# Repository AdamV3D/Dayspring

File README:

The 45° mounts needs to be mirrored pairs for each LED light strip

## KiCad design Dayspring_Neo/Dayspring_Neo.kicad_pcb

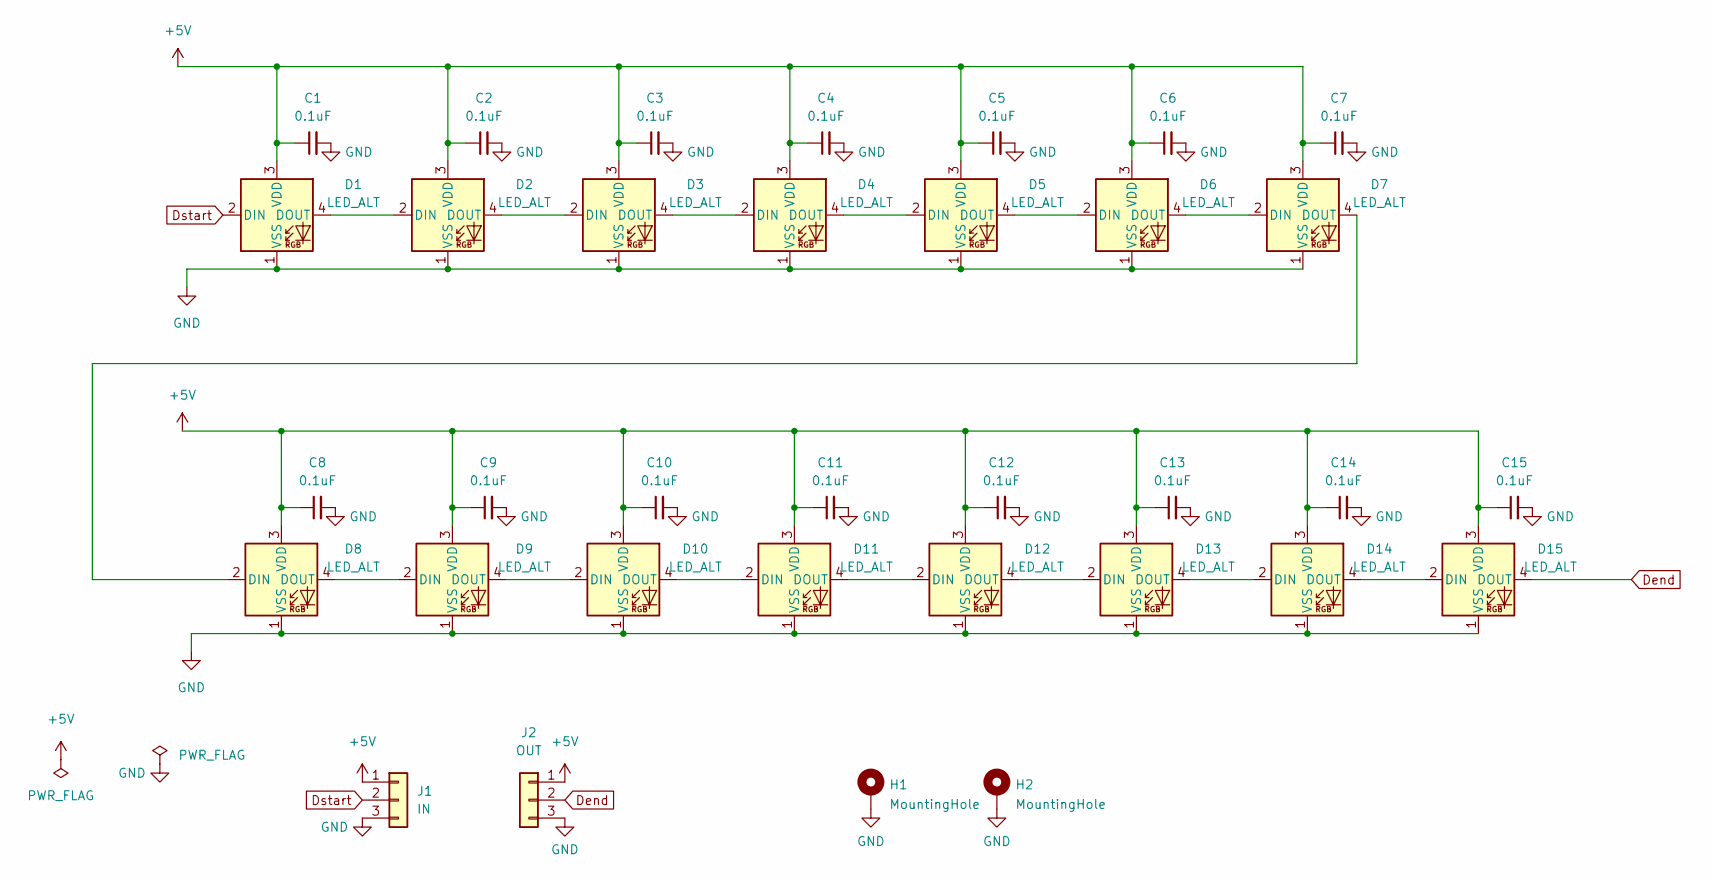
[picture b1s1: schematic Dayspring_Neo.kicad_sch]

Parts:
C1, C2, C3, C4, C5, C6, C7, C8, C9, C10, C11, C12, C13, C14, C15: 0.1uF; C_0805_2012Metric_Pad1.18x1.45mm_HandSolder_V3Dspec; LCSC C28233
D1, D2, D3, D4, D5, D6, D7, D8, D9, D10, D11, D12, D13, D14, D15: LED_ALT; XL-3528RGBW-WS2812B; LCSC C2890364
H1, H2: MountingHole; MountingHole_3.2mm_M3_Pad_Via
J1: IN; JST_XH_S3B-XH-A_1x03_P2.50mm_Horizontal
J2: OUT; JST_XH_S3B-XH-A_1x03_P2.50mm_Horizontal

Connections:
+5V: C1.1, C2.1, C3.1, C4.1, C5.1, C6.1, C7.1, C8.1, C9.1, C10.1, C11.1, C12.1, C13.1, C14.1, C15.1, D1.3 (VDD), D2.3 (VDD), D3.3 (VDD), D4.3 (VDD), D5.3 (VDD), D6.3 (VDD), D7.3 (VDD), D8.3 (VDD), D9.3 (VDD), D10.3 (VDD), D11.3 (VDD), D12.3 (VDD), D13.3 (VDD), D14.3 (VDD), D15.3 (VDD), J1.1, J2.1
Dend: D15.4 (DOUT), J2.2
Dstart: D1.2 (DIN), J1.2
GND: C1.2, C2.2, C3.2, C4.2, C5.2, C6.2, C7.2, C8.2, C9.2, C10.2, C11.2, C12.2, C13.2, C14.2, C15.2, D1.1 (VSS), D2.1 (VSS), D3.1 (VSS), D4.1 (VSS), D5.1 (VSS), D6.1 (VSS), D7.1 (VSS), D8.1 (VSS), D9.1 (VSS), D10.1 (VSS), D11.1 (VSS), D12.1 (VSS), D13.1 (VSS), D14.1 (VSS), D15.1 (VSS), H1.1, H2.1, J1.3, J2.3
unnamed: D1.4 (DOUT), D2.2 (DIN)
unnamed: D2.4 (DOUT), D3.2 (DIN)
unnamed: D3.4 (DOUT), D4.2 (DIN)
unnamed: D4.4 (DOUT), D5.2 (DIN)
unnamed: D5.4 (DOUT), D6.2 (DIN)
unnamed: D6.4 (DOUT), D7.2 (DIN)
unnamed: D7.4 (DOUT), D8.2 (DIN)
unnamed: D8.4 (DOUT), D9.2 (DIN)
unnamed: D9.4 (DOUT), D10.2 (DIN)
unnamed: D10.4 (DOUT), D11.2 (DIN)
unnamed: D11.4 (DOUT), D12.2 (DIN)
unnamed: D12.4 (DOUT), D13.2 (DIN)
unnamed: D13.4 (DOUT), D14.2 (DIN)
unnamed: D14.4 (DOUT), D15.2 (DIN)

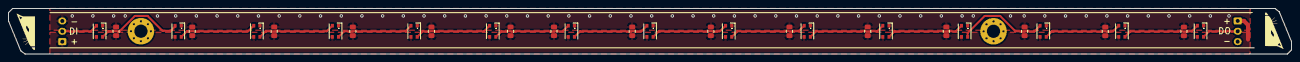
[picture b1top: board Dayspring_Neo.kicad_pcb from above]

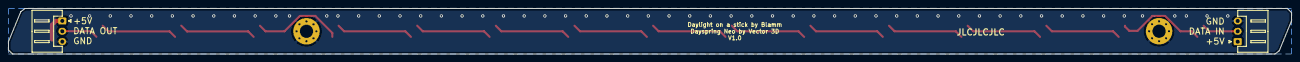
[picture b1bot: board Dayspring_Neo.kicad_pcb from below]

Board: 2 copper layers, 310.0 x 11.0 mm, 34 parts (2 on the bottom side), 18 nets.

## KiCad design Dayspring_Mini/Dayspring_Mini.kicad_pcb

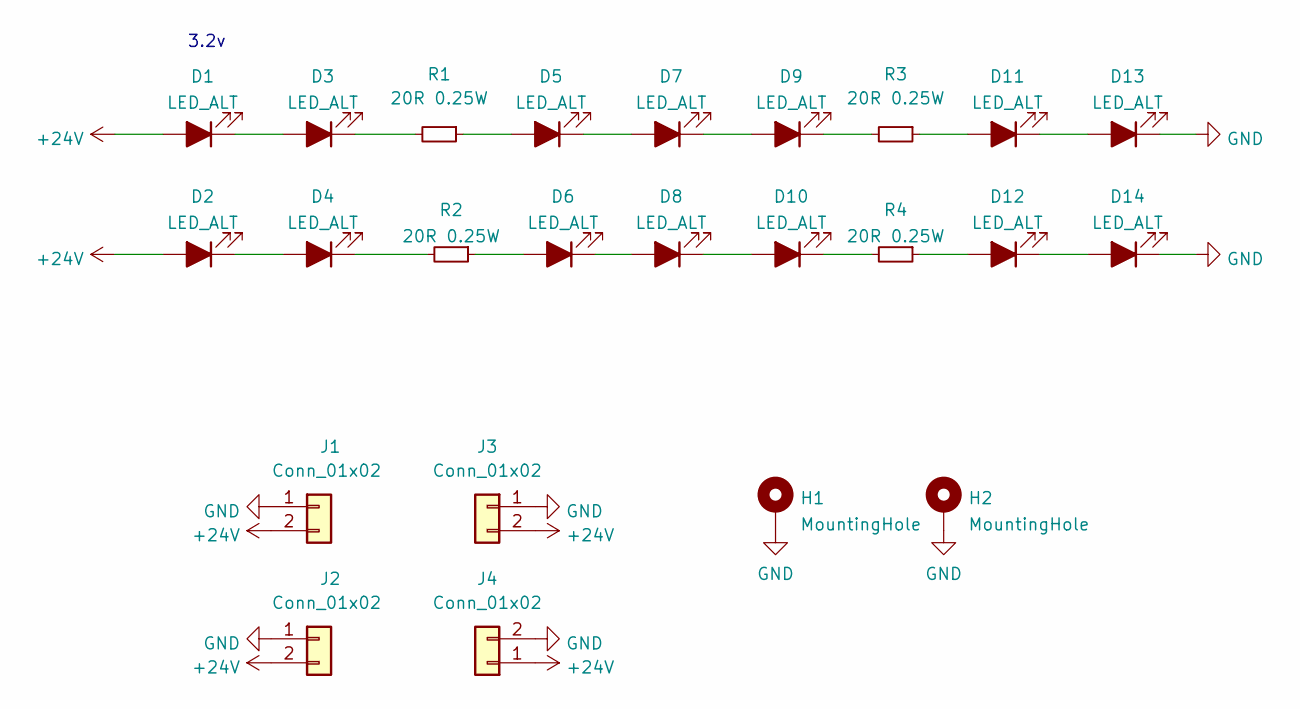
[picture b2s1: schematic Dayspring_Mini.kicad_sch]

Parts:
D1, D2, D3, D4, D5, D6, D7, D8, D9, D10, D11, D12, D13, D14: LED_ALT; LED_PLCC_2835; LCSC C2843876
H1, H2: MountingHole; MountingHole_3.2mm_M3_Pad_Via
J1, J3: Conn_01x02; JST_XH_S2B-XH-A_1x02_P2.50mm_Horizontal; LCSC C157931
J2, J4: Conn_01x02; PinSocket_1x02_P2.54mm_Horizontal; LCSC C2932679
R1, R2, R3, R4: 20R 0.25W; R_1206_3216Metric; LCSC C17955

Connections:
+24V: D1.2 (A), D2.2 (A), J1.2, J2.2, J3.2, J4.1
GND: D13.1 (K), D14.1 (K), H1.1, H2.1, J1.1, J2.1, J3.1, J4.2
unnamed: D1.1 (K), D3.2 (A)
unnamed: D2.1 (K), D4.2 (A)
unnamed: D3.1 (K), R1.2
unnamed: D4.1 (K), R2.2
unnamed: D5.1 (K), D7.2 (A)
unnamed: D5.2 (A), R1.1
unnamed: D6.1 (K), D8.2 (A)
unnamed: D6.2 (A), R2.1
unnamed: D7.1 (K), D9.2 (A)
unnamed: D9.1 (K), R3.2
unnamed: D10.1 (K), R4.2
unnamed: D8.1 (K), D10.2 (A)
unnamed: D11.1 (K), D13.2 (A)
unnamed: D11.2 (A), R3.1
unnamed: D12.1 (K), D14.2 (A)
unnamed: D12.2 (A), R4.1

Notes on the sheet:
3.2v

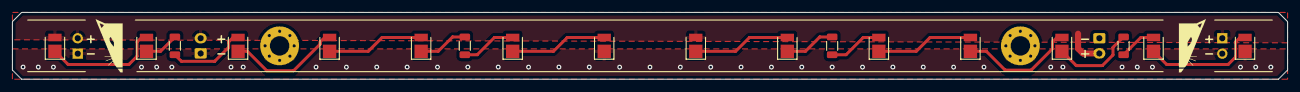
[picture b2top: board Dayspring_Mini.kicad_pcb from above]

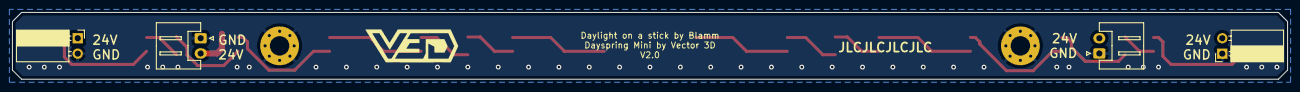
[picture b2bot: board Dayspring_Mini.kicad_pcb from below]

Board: 2 copper layers, 210.0 x 11.0 mm, 24 parts (4 on the bottom side), 18 nets.

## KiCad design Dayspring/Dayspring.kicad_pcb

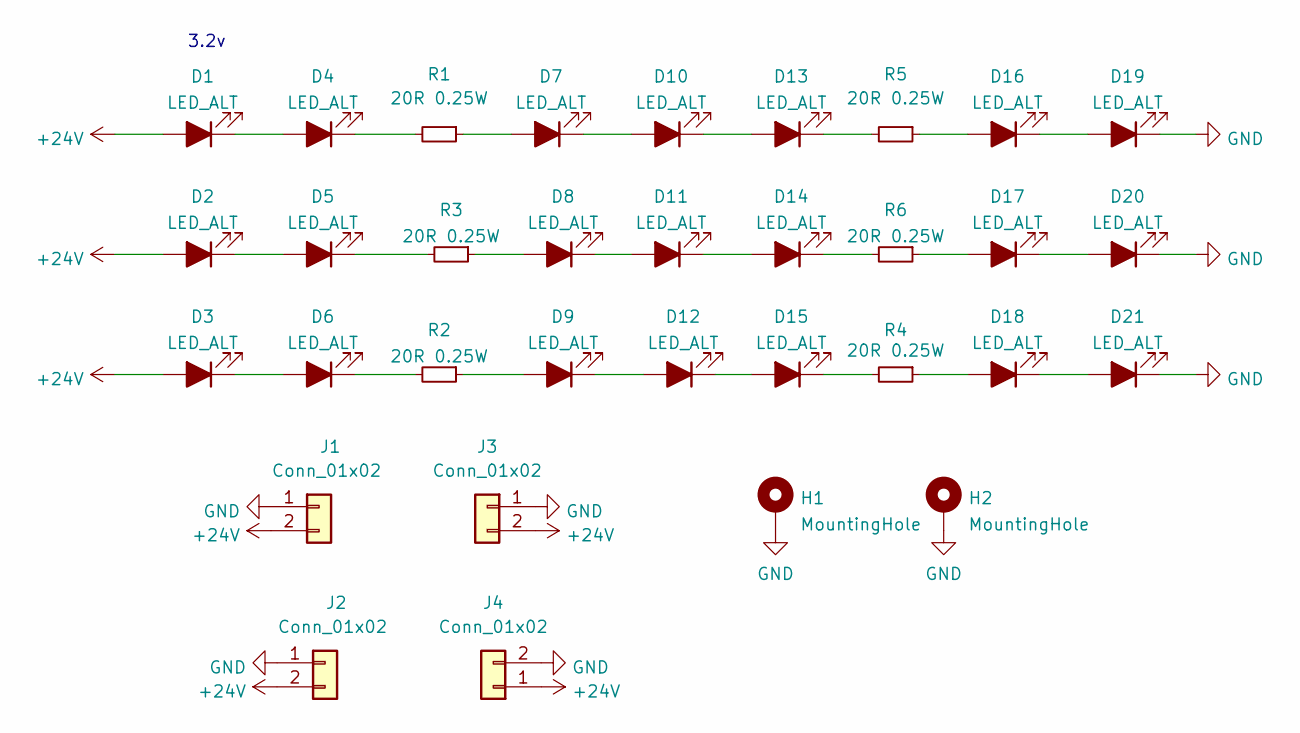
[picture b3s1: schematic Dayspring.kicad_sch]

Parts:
D1, D2, D3, D4, D5, D6, D7, D8, D9, D10, D11, D12, D13, D14, D15, D16, D17, D18, D19, D20, D21: LED_ALT; LED_PLCC_2835; LCSC C2843876
H1, H2: MountingHole; MountingHole_3.2mm_M3_Pad_Via
J1, J3: Conn_01x02; JST_XH_S2B-XH-A_1x02_P2.50mm_Horizontal; LCSC C157931
J2, J4: Conn_01x02; PinSocket_1x02_P2.54mm_Horizontal; LCSC C2932679
R1, R2, R3, R4, R5, R6: 20R 0.25W; R_1206_3216Metric; LCSC C17955

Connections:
+24V: D1.2 (A), D2.2 (A), D3.2 (A), J1.2, J2.2, J3.2, J4.1
GND: D19.1 (K), D20.1 (K), D21.1 (K), H1.1, H2.1, J1.1, J2.1, J3.1, J4.2
unnamed: D1.1 (K), D4.2 (A)
unnamed: D2.1 (K), D5.2 (A)
unnamed: D3.1 (K), D6.2 (A)
unnamed: D4.1 (K), R1.2
unnamed: D5.1 (K), R3.2
unnamed: D6.1 (K), R2.2
unnamed: D7.2 (A), R1.1
unnamed: D8.2 (A), R3.1
unnamed: D9.2 (A), R2.1
unnamed: D10.1 (K), D13.2 (A)
unnamed: D7.1 (K), D10.2 (A)
unnamed: D11.1 (K), D14.2 (A)
unnamed: D8.1 (K), D11.2 (A)
unnamed: D12.1 (K), D15.2 (A)
unnamed: D9.1 (K), D12.2 (A)
unnamed: D13.1 (K), R5.2
unnamed: D14.1 (K), R6.2
unnamed: D15.1 (K), R4.2
unnamed: D16.1 (K), D19.2 (A)
unnamed: D16.2 (A), R5.1
unnamed: D17.1 (K), D20.2 (A)
unnamed: D17.2 (A), R6.1
unnamed: D18.1 (K), D21.2 (A)
unnamed: D18.2 (A), R4.1

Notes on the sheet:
3.2v

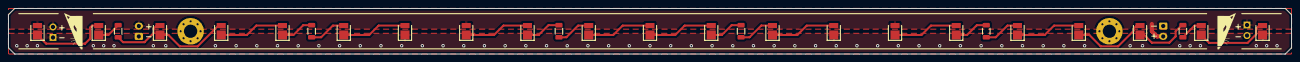
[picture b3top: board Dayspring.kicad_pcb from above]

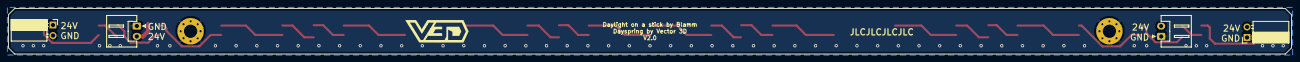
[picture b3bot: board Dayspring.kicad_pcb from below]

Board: 2 copper layers, 310.0 x 11.0 mm, 33 parts (4 on the bottom side), 26 nets.

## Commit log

2023-02-20 Production Version LED and 3030 Mounts
2023-02-20 Mounts Only
2023-02-21 Baffles Added
2023-03-24 Added Lighting control section and macros
2024-01-17 Changed to better fit single LED baffles
2024-01-17 removed
2024-01-17 New single baffle with marking
2024-03-30 Create README
    I know this is a really short README, but this would have been really useful to know before I printed 8 of the same, and inserted heat inserts into them all
2025-01-25 some items removed
2025-01-28 STL files un-removed
